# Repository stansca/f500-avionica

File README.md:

# F-500 — projetos do foguete

Repositórios relacionados: [f500-video-2g4](https://github.com/stansca/f500-video-2g4) · [placa-estatico](https://github.com/stansca/placa-estatico) · [rocket-arduino](https://github.com/stansca/rocket-arduino) · [kicad-biblioteca-js](https://github.com/stansca/kicad-biblioteca-js)

Tudo do F-500 (apogeu ~500 m) fica nesta pasta.

## Placas

| Placa | Pasta | Estado |
|---|---|---|
| Aviônica v1 (rayquasa) | [`rayquasa/`](rayquasa/) | final, só THT |
| Aviônica v2 rev. B (câmera DJI/Walksnail) | [`avionica_f500_v2/`](avionica_f500_v2/) | posicionada; **roteamento manual em andamento** |
| Aviônica v2 **rev. C-V** (controle do vídeo 2,4 GHz) | [`avionica_f500_v2_video/`](avionica_f500_v2_video/) | variante da rev. B, roteamento preservado |
| Aviônica v2 rev. C-SV (sem vídeo) | [`avionica_f500_v2_sem_video/`](avionica_f500_v2_sem_video/) | variante da rev. B, roteamento preservado |
| **RF-FEM 2,4 GHz** (vídeo) | [f500-video-2g4 / placa_rf_fem](https://github.com/stansca/f500-video-2g4/tree/main/Hardware/placa_rf_fem) | gerada; cadeia de RF traçada, falta rotear alimentação/controle |
| **Alimentação do vídeo** | [f500-video-2g4 / placa_alim_video](https://github.com/stansca/f500-video-2g4/tree/main/Hardware/placa_alim_video) | gerada; falta rotear |

As duas placas do vídeo ficam dentro de `video_2g4_f500/Hardware/` porque compartilham a biblioteca de símbolos (`Hardware/biblioteca/`) e o gerador (`Hardware/gerador/`). A estrutura segue o padrão dos repositórios da equipe (Hardware / Firmware / Software).

## Sistema de vídeo ao vivo 2,4 GHz

Repositório [f500-video-2g4](https://github.com/stansca/f500-video-2g4) (localmente em `video_2g4_f500/`): placas RF-FEM e de alimentação, software da Pi Zero 2W, dos SDRs (openwifi) e do notebook, e firmware da ESP32.
Documento completo: [Video_2G4_F500_Documentacao.pdf](https://github.com/stansca/f500-video-2g4/blob/main/docs/Video_2G4_F500_Documentacao.pdf).

```
avionica_f500_v2_video (J4) ──XH-4──> placa_alim_video (J2) ──> Pi Zero 2W / ADRV1CRR-BOB / placa_rf_fem
```

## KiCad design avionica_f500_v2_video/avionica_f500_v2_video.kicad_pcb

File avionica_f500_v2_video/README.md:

# Aviônica F-500 v2 — rev. C-V (com vídeo ao vivo 2,4 GHz)

Variante da [rev. B](../avionica_f500_v2/) que leva em conta o documento **"Transmissão de vídeo"** (câmera Global Shutter → Pi Zero 2W → ADRV1CRR-BOB + ADRV9361-Z7035 → FEM SKY85333-11 → filtro ZVBP-2400-S+ → antena Taoglas FXP73, 802.11 OFDM em 2,4 GHz, UDP multicast). A variante sem vídeo está em [`../avionica_f500_v2_sem_video/`](../avionica_f500_v2_sem_video/).

Feita a partir da PCB da rev. B **com o roteamento manual preservado** (`scripts/delta_pcb.py`). Só foram apagadas as trilhas da antiga chave da câmera.

## O que mudou em relação à rev. B (bloco 3)
| rev. B (câmera DJI/Walksnail) | rev. C-V (vídeo do PDF) |
|---|---|
| Q3 AO3401A chaveava VBAT da câmera (até ~1,6 A) pelo J4 | **Removidos Q3, R3, C10, C11.** O vídeo do PDF consome vários ampères em 5 V e **não passa por esta placa** |
| J4: VBAT_CAM, GND, TX, RX | **J4 (JST-XH 4):** 1 `VID_OFF` · 2 GND · 3 `PI_RXD` · 4 `PI_TXD` |
| Q4 AO3400A acionava o gate do Q3 | **Q4 AO3400A em dreno aberto:** com IO4 em HIGH, puxa para GND o pino EN do regulador do vídeo e desliga o vídeo |
| UART direta | **R20/R21 1 kΩ em série** na UART: protegem a Pi quando ela está desligada e a ESP32 transmite (alimentação parasita pelos diodos de proteção) |

**Pinos:** IO4 = `VID_OFF` (antigo CAM_EN), IO25 = `VID_TX` → GPIO15 (RXD) da Pi, IO13 = `VID_RX` ← GPIO14 (TXD) da Pi. Tudo em 3,3 V nos dois lados.

### Por que a alimentação do vídeo fica fora da placa
- **Consumo:** a Pi Zero 2W pede fonte de 5 V/2,5 A. A ADRV1CRR-BOB recebe 5 V e gera os rails do ADRV9361. O PDF diz que o SOM consome 240–820 mA transmitindo. O FEM a +28 dBm consome algumas centenas de mA. Somando, o vídeo precisa de **um regulador 5 V de ≥5 A**.
- **Limite da rev. B:** a chave principal (JST-XH, 3 A), o diodo SS34 (3 A) e o buck MP1584 (3 A) da aviônica não aguentam essa carga.
- **Recomendação:** **bateria 2S própria para o vídeo + regulador 5 V/5 A com pino EN** (ex.: Pololu D36V50F5). O GND do vídeo é ligado ao GND desta placa pelo pino 2 do J4, que é a referência da UART.
- **Independência:** com a ESP32 em reset ou boot, o R4 segura o Q4 desligado e o EN fica solto. **O vídeo funciona mesmo se a aviônica falhar**, e uma falha no vídeo não derruba a recuperação.
- **Confira a lógica do EN do regulador escolhido.** O esperado é EN com pull-up interno, em que nível baixo desliga.

### Desligar sem corromper o SD da Pi
Antes de puxar o `VID_OFF`, a ESP32 manda `SHUTDOWN` pela UART e espera ~10 s. A Pi deve rodar um serviço que lê a serial e executa `poweroff`.

### O que fica em outras placas (conforme o PDF)
- **FEM SKY85333-11** (substituto do SKY85354-11, que foi descontinuado) numa placa de RF própria: microfita/CPW de 50 Ω, LGA 3 × 5 mm. Os sinais de TX/RX enable vêm do SDR, não da ESP32.
- **Filtro de cavidade ZVBP-2400-S+** (SMA) e antena Taoglas FXP73 (U.FL/MHF I), colada em seção radiotransparente.

### Pontos do PDF que precisam de atenção
1. **Canal Wi-Fi:** o filtro passa só **2375–2425 MHz**. Com 20 MHz de largura, só o **canal 1** (2401–2423 MHz) cabe inteiro na banda. Os canais 6 e 11 seriam cortados.
2. **Potência:** o PDF fala em +28 dBm (FEM em MCS0, EIRP 33 dBm) e, em outros trechos, em "1 W (+30 dBm)" (EIRP 35 dBm). As duas ficam abaixo de 36 dBm (Res. ANATEL 680/2017), mas o projeto precisa fixar uma delas e travar a atenuação do AD9361.
3. **Norma:** o texto cita 802.11g/n (OFDM 20 MHz) e, no item do detector, 802.11ax. Vale padronizar em g/n.
4. **Escala:** o PDF mira 4 km de distância, e o F-500 sobe ~500 m. Confira peso e volume (BOB + SOM + Pi + filtro de cavidade + bateria) contra a seção de carga útil.
5. **Interferência:** o PA de 2,4 GHz perto da antena do GPS (1575 MHz) e do LoRa (917 MHz) pode dessensibilizar os receptores. Afaste as antenas e mantenha o Wi-Fi/BT da ESP32 desligado.

## O que mudou para seguir o guia
| Guia | Rev. B |
|---|---|
| Esquemático em blocos, ligados por labels globais | 7 blocos com borda tracejada e título. Dentro de cada bloco, as ligações são fios; entre blocos, labels globais. GND/+5V/+3V3 usam símbolos de alimentação |
| Valor e datasheet dos componentes | Todos têm valor. Os CIs têm datasheet (ESP32, RFM95W, BMP280, MP1584, AO3400A/AO3401A, SS34, microSD) |
| 100 nF junto de cada alimentação | ESP32 (3V3 e 5V), RFM95W (10 µF + 100 nF), BMP280, microSD (10 µF + 100 nF), GPS e saída do buck |
| Regras do fabricante | Configurações do modelo **PCBWay** (2 camadas, 1 oz) importadas no `.kicad_pro`, com o `.kicad_dru` do PCBWay |
| Trilhas pela corrente | Classes de rede (tabela abaixo). Estimativa de corrente anotada no esquemático |
| Até 100 × 100 mm | **60 × 100 mm**: cabe na faixa mais barata e num tubo de ~75 mm |
| Componentes ruidosos longe do rádio | Buck embaixo, LoRa e GPS em cima, separados pelo ESP32. Área sem cobre sob a antena do ESP32 |

## Estimativa de corrente (pior caso)
- **Consumo em 5 V** (via buck): ESP32 250 mA + RFM95W 120 mA + microSD 100 mA + GPS 45 mA + buzzer 30 mA + sensores 6 mA ≈ **550 mA**.
- **Entrada do buck** (80 % de eficiência, 2S descarregada em 6,4 V): **0,54 A**.
- **Vídeo**: alimentado à parte (bateria + regulador 5 V/5 A próprios); por esta placa passam só mA.
- **Pulso do ignitor**: ~3 A.

| Classe | Nets | Trilha |
|---|---|---|
| Bateria | VBAT_IN, VBAT_SW, VBAT, GND | 1,2 mm |
| Pyro | VBAT_ARM, PYRO1_D, PYRO2_D | 1,0 mm |
| Alim_5V / Alim_3V3 | +5V / +3V3 | 0,6 / 0,5 mm |
| RF_50ohm | LORA_ANT | 2,8 mm, curta, com GND em volta |
| Default | sinais | 0,25 mm |

## Peças
- **Montagem:** SMD 0805/SOT-23/SMA com pads *HandSolder*, que dá para soldar no ferro.
- **Módulos:** ESP32-DevKitC, RFM95W, BMP280 e MP1584EN.
- **Conectores:** XT30 para a bateria, bornes de 3,5 mm para os ignitores e JST-XH para chaves, GPS, I2C e vídeo.
- **microSD:** soquete Molex 104031 a 3,3 V direto. Isso elimina o problema de MISO do módulo SD com level shifter.
- **MOSFETs:** AO3400A nos ignitores (pulso de 30 A) e no VID_OFF do vídeo (dreno aberto).
- **Embaixo do DevKit**, que fica em barra fêmea de 8,5 mm, ficam só SMD baixos: o divisor da bateria, os resistores dos LEDs e o driver do buzzer. Há uma regra de DRC que libera essa sobreposição de courtyard.
- Lista completa em `docs/BOM.csv`.

## Estado (09/11/2026)
- ERC: **0 erros** (os mesmos 6 avisos de tipo de pino da rev. B). Paridade esquemático↔PCB: **0**.
- DRC: nenhum tipo de erro novo em relação à rev. B. Continuam os avisos de serigrafia, as ligações por rotear e duas trilhas soltas que já existiam na rev. B (I2C_SDA e um toco de SPI_MOSI).
- Firmware de teste compila (core esp32).

## Antes de fabricar
- **Conferir a furação do módulo MP1584** com o módulo comprado. O footprint `F500v2:MP1584_Modulo` tem pads a ±9,5 × ±6,5 mm, o que é suposição.
- Confirmar a lógica do EN do regulador 5 V/5 A do vídeo e que o tubo comporta 60 × 100 mm e o conjunto de vídeo.
- O firmware não muda em relação à rev. A: use `firmware/pinos_f500_v2.h`. Mande a tensão da bateria por célula para o pacote continuar compatível com o tracker.

## Regenerar
`scripts/delta_pcb.py` aplica mudanças do `design.py` na PCB já roteada sem perder trilhas (é o que gerou esta variante). `scripts/build.sh` gera tudo do zero a partir de `scripts/design.py` (netlist e blocos) e `scripts/pcb_pos.py` (posições). Ele confere a netlist e roda ERC/DRC. **Ele sobrescreve a PCB**: depois de começar a rotear, edite pelo KiCad.

> `docs/Avionica_F-500_v2_Documentacao.pdf` descreve a rev. B, com a câmera DJI. As diferenças estão neste README. O PDF da antena tracker continua válido.

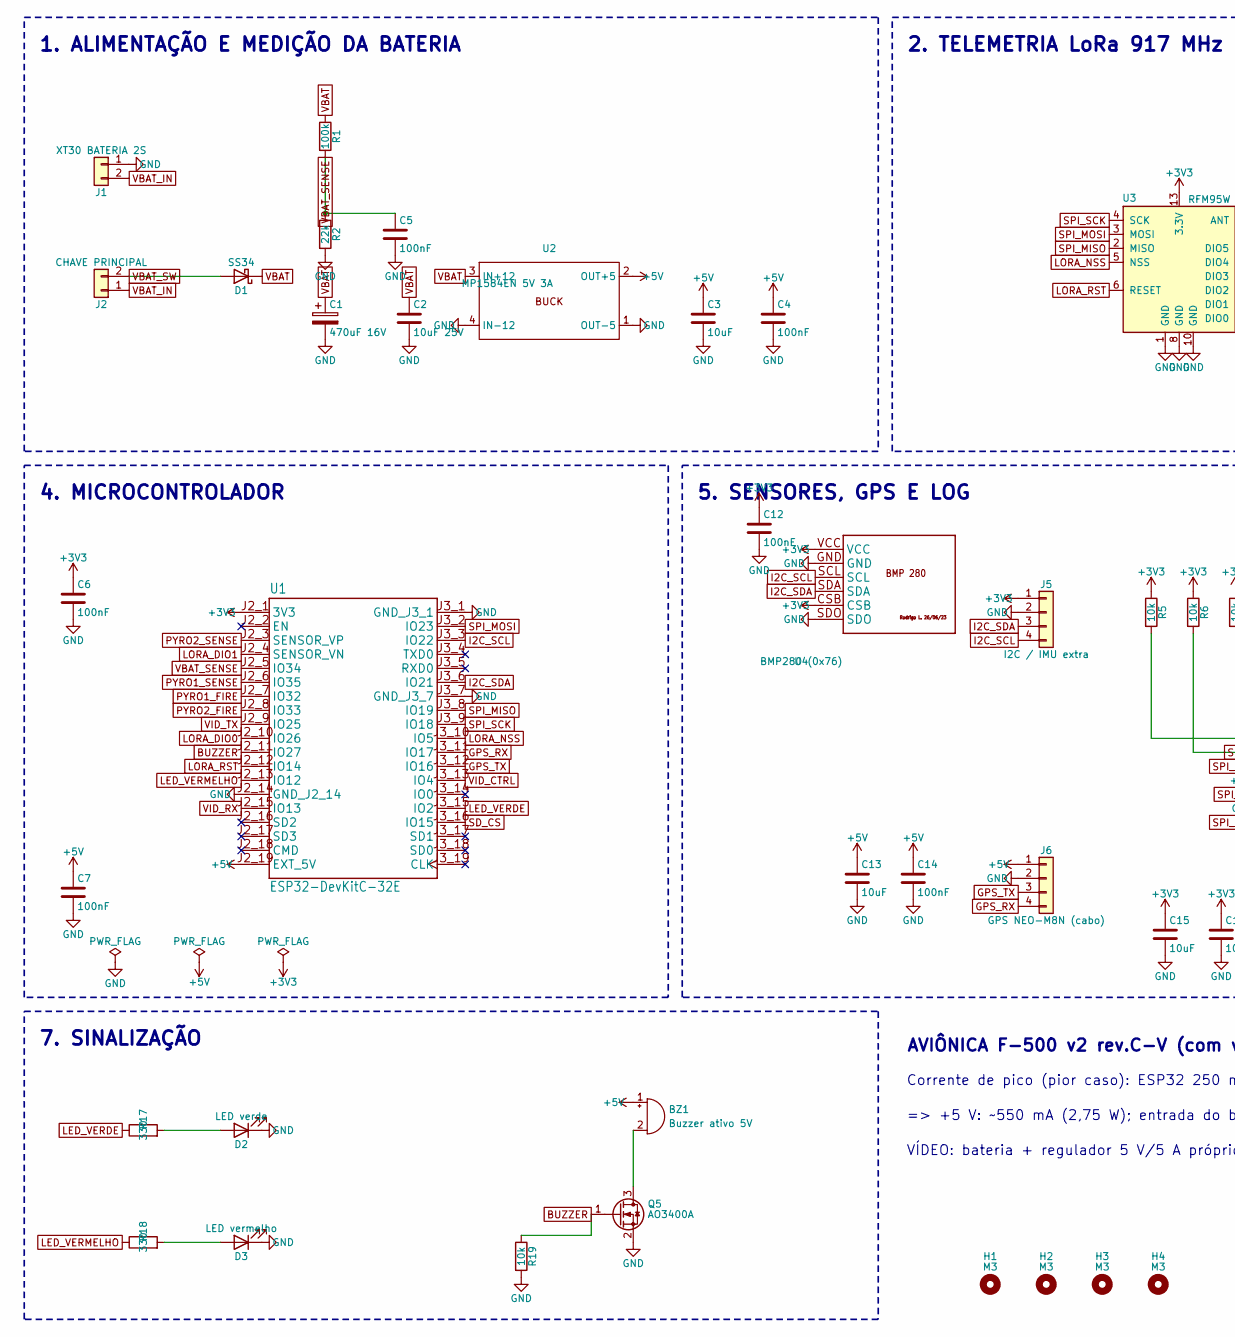
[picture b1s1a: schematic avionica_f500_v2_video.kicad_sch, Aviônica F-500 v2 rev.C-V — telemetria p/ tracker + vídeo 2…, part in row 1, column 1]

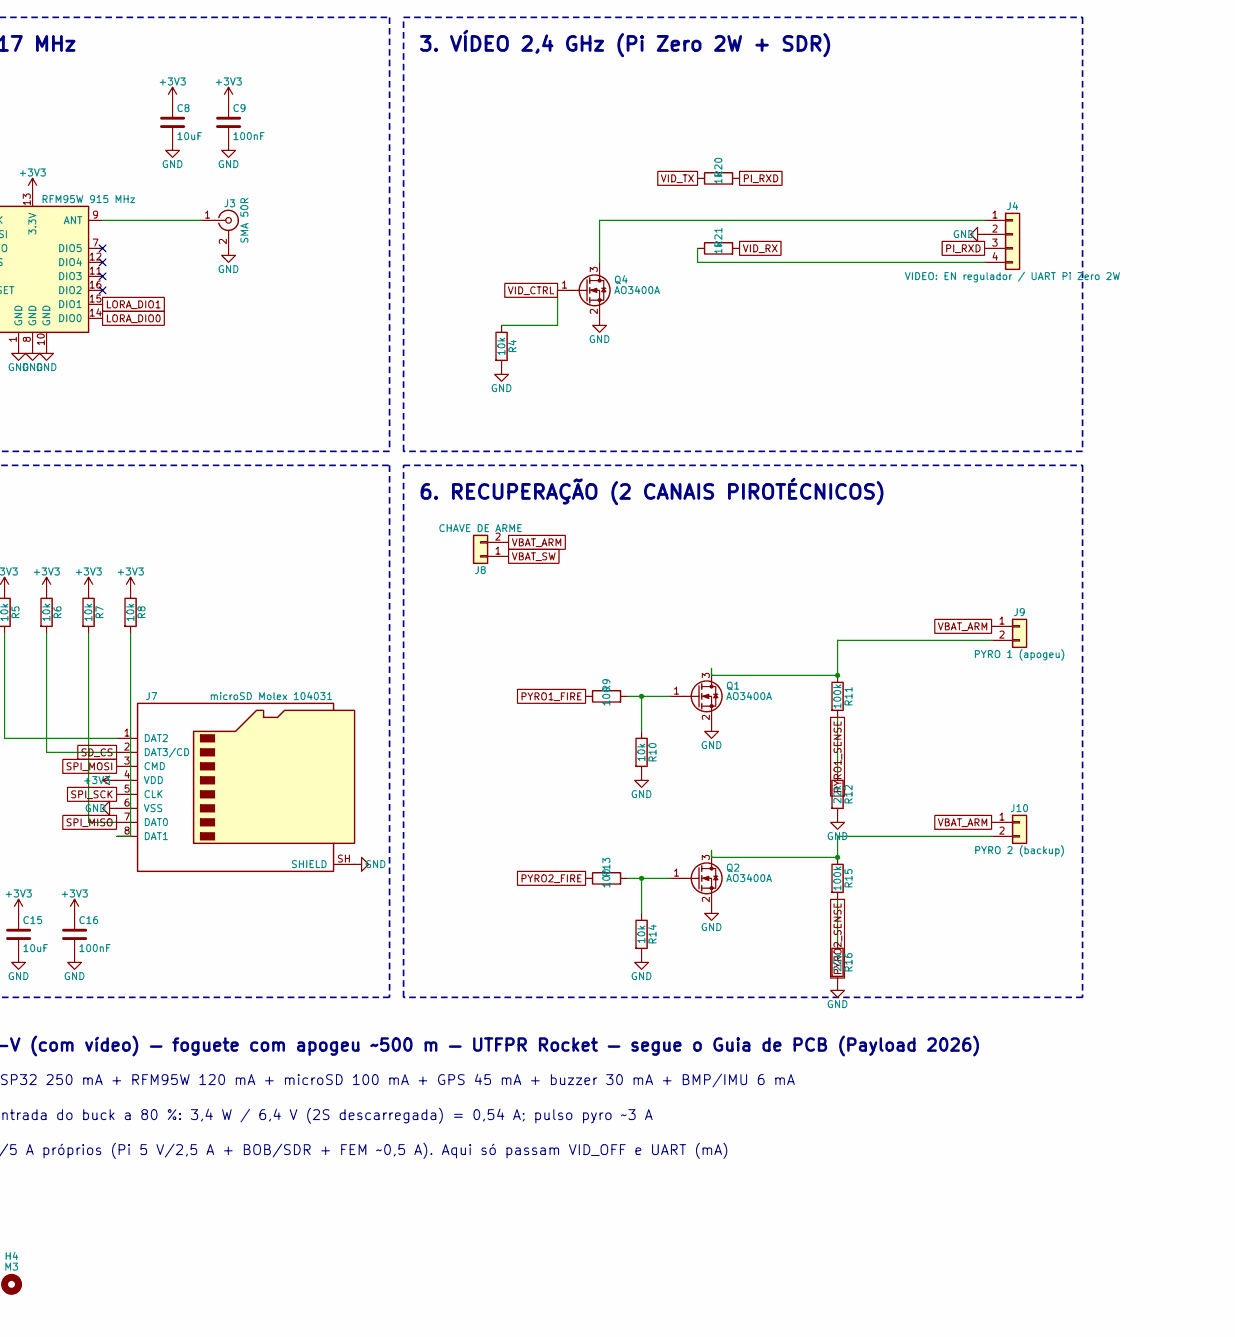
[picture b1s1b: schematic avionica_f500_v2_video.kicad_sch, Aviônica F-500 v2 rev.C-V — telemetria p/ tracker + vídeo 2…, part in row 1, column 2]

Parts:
BZ1: Buzzer ativo 5V; Buzzer_12x9.5RM7.6
C1: 470uF 16V; CP_Radial_D8.0mm_P3.50mm
C2: 10uF 25V; C_1206_3216Metric_Pad1.33x1.80mm_HandSolder
C3: 10uF; C_1206_3216Metric_Pad1.33x1.80mm_HandSolder
C4, C5, C6, C7, C9, C12, C14, C16: 100nF; C_0805_2012Metric_Pad1.18x1.45mm_HandSolder
C8, C13, C15: 10uF; C_0805_2012Metric_Pad1.18x1.45mm_HandSolder
D1: SS34; D_SMA_Handsoldering
D2: LED verde; LED_0805_2012Metric_Pad1.15x1.40mm_HandSolder
D3: LED vermelho; LED_0805_2012Metric_Pad1.15x1.40mm_HandSolder
H1, H2, H3, H4: M3; MountingHole_3.2mm_M3
J1: XT30 BATERIA 2S; AMASS_XT30PW-M_1x02_P2.50mm_Horizontal
J2: CHAVE PRINCIPAL; JST_XH_B2B-XH-A_1x02_P2.50mm_Vertical
J3: SMA 50R; SMA_Amphenol_132289_EdgeMount
J4: VIDEO: EN regulador / UART Pi Zero 2W; JST_XH_B4B-XH-A_1x04_P2.50mm_Vertical
J5: I2C / IMU extra; JST_XH_B4B-XH-A_1x04_P2.50mm_Vertical
J6: GPS NEO-M8N (cabo); JST_XH_B4B-XH-A_1x04_P2.50mm_Vertical
J7: microSD Molex 104031; microSD_HC_Molex_104031-0811
J8: CHAVE DE ARME; JST_XH_B2B-XH-A_1x02_P2.50mm_Vertical
J9: PYRO 1 (apogeu); TerminalBlock_Phoenix_PT-1,5-2-3.5-H_1x02_P3.50mm_Horizontal
J10: PYRO 2 (backup); TerminalBlock_Phoenix_PT-1,5-2-3.5-H_1x02_P3.50mm_Horizontal
Q1, Q2, Q4, Q5: AO3400A; SOT-23
R1, R11, R15: 100k; R_0805_2012Metric_Pad1.20x1.40mm_HandSolder
R2, R12, R16: 22k; R_0805_2012Metric_Pad1.20x1.40mm_HandSolder
R4, R5, R6, R7, R8, R10, R14, R19: 10k; R_0805_2012Metric_Pad1.20x1.40mm_HandSolder
R9, R13: 100; R_0805_2012Metric_Pad1.20x1.40mm_HandSolder
R17, R18: 330; R_0805_2012Metric_Pad1.20x1.40mm_HandSolder
R20, R21: 1k; R_0805_2012Metric_Pad1.20x1.40mm_HandSolder
U1: ESP32-DevKitC-32E
U2: MP1584EN 5V 3A; MP1584_Modulo
U3: RFM95W 915 MHz; HOPERF_RFM9XW_SMD
U4: BMP280 (0x76); BMP280_Modulo

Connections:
+3V3: C6.1, C8.1, C9.1, C12.1, C15.1, C16.1, J5.1, J7.4 (VDD), R5.1, R6.1, R7.1, R8.1, U1.J2_1 (3V3), U3.13 (3.3V), U4.CSB, U4.VCC
+5V: BZ1.1 (+), C3.1, C4.1, C7.1, C13.1, C14.1, J6.1, U1.J2_19 (EXT_5V), U2.2 (OUT+5)
BUZZER: Q5.1 (G), R19.1, U1.J2_11 (IO27)
GND: C1.2, C2.2, C3.2, C4.2, C5.2, C6.2, C7.2, C8.2, C9.2, C12.2, C13.2, C14.2, C15.2, C16.2, D2.1 (K), D3.1 (K), J1.1, J3.2 (Ext), J4.2, J5.2, J6.2, J7.6 (VSS), J7.SH (SHIELD), Q1.2 (S), Q2.2 (S), Q4.2 (S), Q5.2 (S), R2.2, R4.2, R10.2, R12.2, R14.2, R16.2, R19.2, U1.J2_14 (GND_J2_14), U1.J3_1 (GND_J3_1), U1.J3_7 (GND_J3_7), U2.1 (OUT-5), U2.4 (IN-12), U3.1 (GND), U3.8 (GND), U3.10 (GND), U4.GND, U4.SDO
GPS_RX: J6.4, U1.J3_11 (IO17)
GPS_TX: J6.3, U1.J3_12 (IO16)
I2C_SCL: J5.4, U1.J3_3 (IO22), U4.SCL
I2C_SDA: J5.3, U1.J3_6 (IO21), U4.SDA
LED_VERDE: R17.1, U1.J3_15 (IO2)
LED_VERMELHO: R18.1, U1.J2_13 (IO12)
LORA_DIO0: U1.J2_10 (IO26), U3.14 (DIO0)
LORA_DIO1: U1.J2_4 (SENSOR_VN), U3.15 (DIO1)
LORA_NSS: U1.J3_10 (IO5), U3.5 (NSS)
LORA_RST: U1.J2_12 (IO14), U3.6 (RESET)
unnamed: BZ1.2 (-), Q5.3 (D)
unnamed: D2.2 (A), R17.2
unnamed: D3.2 (A), R18.2
unnamed: J3.1 (In), U3.9 (ANT)
unnamed: J4.1, Q4.3 (D)
unnamed: J4.4, R21.1
unnamed: J7.8 (DAT1), R8.2
unnamed: J7.1 (DAT2), R5.2
unnamed: J9.2, Q1.3 (D), R11.1
unnamed: J10.2, Q2.3 (D), R15.1
unnamed: Q1.1 (G), R9.2, R10.1
unnamed: Q2.1 (G), R13.2, R14.1
PI_RXD: J4.3, R20.2
PYRO1_FIRE: R9.1, U1.J2_7 (IO32)
PYRO1_SENSE: R11.2, R12.1, U1.J2_6 (IO35)
PYRO2_FIRE: R13.1, U1.J2_8 (IO33)
PYRO2_SENSE: R15.2, R16.1, U1.J2_3 (SENSOR_VP)
SD_CS: J7.2 (DAT3/CD), R6.2, U1.J3_16 (IO15)
SPI_MISO: J7.7 (DAT0), R7.2, U1.J3_8 (IO19), U3.2 (MISO)
SPI_MOSI: J7.3 (CMD), U1.J3_2 (IO23), U3.3 (MOSI)
SPI_SCK: J7.5 (CLK), U1.J3_9 (IO18), U3.4 (SCK)
VBAT: C1.1, C2.1, D1.1 (K), R1.1, U2.3 (IN+12)
VBAT_ARM: J8.2, J9.1, J10.1
VBAT_IN: J1.2, J2.1
VBAT_SENSE: C5.1, R1.2, R2.1, U1.J2_5 (IO34)
VBAT_SW: D1.2 (A), J2.2, J8.1
VID_CTRL: Q4.1 (G), R4.1, U1.J3_13 (IO4)
VID_RX: R21.2, U1.J2_15 (IO13)
VID_TX: R20.1, U1.J2_9 (IO25)

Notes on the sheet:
1. ALIMENTAÇÃO E MEDIÇÃO DA BATERIA
2. TELEMETRIA LoRa 917 MHz
3. VÍDEO 2,4 GHz (Pi Zero 2W + SDR)
4. MICROCONTROLADOR
5. SENSORES, GPS E LOG
6. RECUPERAÇÃO (2 CANAIS PIROTÉCNICOS)
7. SINALIZAÇÃO
AVIÔNICA F-500 v2 rev.C-V (com vídeo) — foguete com apogeu ~500 m — UTFPR Rocket — segue o Guia de PCB (Payload 2026)
Corrente de pico (pior caso): ESP32 250 mA + RFM95W 120 mA + microSD 100 mA + GPS 45 mA + buzzer 30 mA + BMP/IMU 6 mA
=> +5 V: ~550 mA (2,75 W); entrada do buck a 80 %: 3,4 W / 6,4 V (2S descarregada) = 0,54 A; pulso pyro ~3 A
VÍDEO: bateria + regulador 5 V/5 A próprios (Pi 5 V/2,5 A + BOB/SDR + FEM ~0,5 A). Aqui só passam VID_OFF e UART (mA)

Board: 2 copper layers, 60 parts (0 on the bottom side), 43 nets, no tracks yet.

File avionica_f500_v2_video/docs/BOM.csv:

"Reference","Value","Footprint","QUANTITY"
"BZ1","Buzzer ativo 5V","Buzzer_Beeper:Buzzer_12x9.5RM7.6","1"
"C1","470uF 16V","Capacitor_THT:CP_Radial_D8.0mm_P3.50mm","1"
"C2","10uF 25V","Capacitor_SMD:C_1206_3216Metric_Pad1.33x1.80mm_HandSolder","1"
"C3","10uF","Capacitor_SMD:C_1206_3216Metric_Pad1.33x1.80mm_HandSolder","1"
"C4-C7,C9,C12,C14,C16","100nF","Capacitor_SMD:C_0805_2012Metric_Pad1.18x1.45mm_HandSolder","8"
"C8,C13,C15","10uF","Capacitor_SMD:C_0805_2012Metric_Pad1.18x1.45mm_HandSolder","3"
"D1","SS34","Diode_SMD:D_SMA_Handsoldering","1"
"D2","LED verde","LED_SMD:LED_0805_2012Metric_Pad1.15x1.40mm_HandSolder","1"
"D3","LED vermelho","LED_SMD:LED_0805_2012Metric_Pad1.15x1.40mm_HandSolder","1"
"J1","XT30 BATERIA 2S","Connector_AMASS:AMASS_XT30PW-M_1x02_P2.50mm_Horizontal","1"
"J2","CHAVE PRINCIPAL","Connector_JST:JST_XH_B2B-XH-A_1x02_P2.50mm_Vertical","1"
"J3","SMA 50R","Connector_Coaxial:SMA_Amphenol_132289_EdgeMount","1"
"J4","VIDEO: EN regulador / UART Pi Zero 2W","Connector_JST:JST_XH_B4B-XH-A_1x04_P2.50mm_Vertical","1"
"J5","I2C / IMU extra","Connector_JST:JST_XH_B4B-XH-A_1x04_P2.50mm_Vertical","1"
"J6","GPS NEO-M8N (cabo)","Connector_JST:JST_XH_B4B-XH-A_1x04_P2.50mm_Vertical","1"
"J7","microSD Molex 104031","Connector_Card:microSD_HC_Molex_104031-0811","1"
"J8","CHAVE DE ARME","Connector_JST:JST_XH_B2B-XH-A_1x02_P2.50mm_Vertical","1"
"J9","PYRO 1 (apogeu)","TerminalBlock_Phoenix:TerminalBlock_Phoenix_PT-1,5-2-3.5-H_1x02_P3.50mm_Horizontal","1"
"J10","PYRO 2 (backup)","TerminalBlock_Phoenix:TerminalBlock_Phoenix_PT-1,5-2-3.5-H_1x02_P3.50mm_Horizontal","1"
"Q1,Q2,Q4,Q5","AO3400A","Package_TO_SOT_SMD:SOT-23","4"
"R1,R11,R15","100k","Resistor_SMD:R_0805_2012Metric_Pad1.20x1.40mm_HandSolder","3"
"R2,R12,R16","22k","Resistor_SMD:R_0805_2012Metric_Pad1.20x1.40mm_HandSolder","3"
"R4-R8,R10,R14,R19","10k","Resistor_SMD:R_0805_2012Metric_Pad1.20x1.40mm_HandSolder","8"
"R9,R13","100","Resistor_SMD:R_0805_2012Metric_Pad1.20x1.40mm_HandSolder","2"
"R17,R18","330","Resistor_SMD:R_0805_2012Metric_Pad1.20x1.40mm_HandSolder","2"
"R20,R21","1k","Resistor_SMD:R_0805_2012Metric_Pad1.20x1.40mm_HandSolder","2"
"U1","ESP32-DevKitC-32E","JS_Microcontroladores:ESP32-DevKitC-32E","1"
"U2","MP1584EN 5V 3A","F500v2:MP1584_Modulo","1"
"U3","RFM95W 915 MHz","RF_Module:HOPERF_RFM9XW_SMD","1"
"U4","BMP280 (0x76)","JS_Sensores:BMP280_Modulo","1"

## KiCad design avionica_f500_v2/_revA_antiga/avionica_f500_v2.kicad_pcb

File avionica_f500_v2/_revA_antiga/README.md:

# Aviônica F-500 v2

Computador de bordo para o foguete F-500 (apogeu de ~500 m). É a evolução da `rayquasa` (F-500 v1) com:

- **Telemetria compatível com a antena tracker**: RFM95W (SX1276) a 917 MHz nos **mesmos GPIOs do `tracker_rx`**, com o mesmo pacote de 26 bytes a 5 Hz.
- **Câmera/VTX digital**: conector próprio com VBAT 2S chaveado pelo ESP32 e UART para MSP/OSD.
- **2 canais de recuperação** com MOSFET de porta lógica, leitura de continuidade e chave de arme física.
- GPS por cabo, BMP280, microSD para log e conector I2C extra para IMU.

PCB de 2 camadas, **60 × 170 mm**, quase tudo THT ou módulo. A única peça SMD é o RFM95W, que tem bordas castelladas e dá para soldar no ferro. Os furos M3 ficam nas posições H1–H4.

## Arquivos
| Arquivo | O que é |
|---|---|
| `avionica_f500_v2.kicad_sch/.kicad_pcb/.kicad_pro` | Projeto KiCad 10 |
| `docs/esquematico.pdf`, `docs/pcb_*.png`, `docs/BOM.csv` | Saídas para revisão e compra |
| `firmware/pinos_f500_v2.h` | Pinagem para portar o `foguete_tx.ino` |
| `scripts/` | Gerador (`design.py` = netlist + posições). `build.sh` regenera **e sobrescreve a PCB** |

## Estado
- ERC: 0 erros. Ficam 7 avisos de tipo de pino, que vêm dos símbolos de módulo da biblioteca JS.
- Paridade esquemático ↔ PCB: 0 problemas.
- **Falta rotear.** São 71 ligações em ratsnest. Os planos de GND nas duas faces já estão criados.
- O DRC acusa 5 violações de "borda" no J3. Isso é esperado, porque o SMA de borda precisa encostar na borda. Exclua essas violações no DRC do KiCad. Os avisos de serigrafia sobre pad vêm dos footprints da biblioteca.

### Roteamento sugerido
1. Abra no KiCad. As classes de rede já estão configuradas: Potência com 1,0 mm (VBAT*, PYRO*_D, +5V, GND), 3V3 com 0,6 mm e RF com 2,8 mm.
2. Rote primeiro **à mão**: LORA_ANT (do pino 9 do RFM até o SMA, curto e reto, com GND dos dois lados), VBAT_SW→ARM→PYRO, VBAT→Q3→J9.
3. O resto pode ir no Freerouting (plugin do KiCad) ou à mão. Depois, preencha as zonas (B).

## Pinagem (ESP32-DevKitC)
| Função | GPIO | Observação |
|---|---|---|
| LoRa SCK/MISO/MOSI/NSS | 18/19/23/5 | igual ao tracker_rx |
| LoRa DIO0 / RST / DIO1 | 26 / 14 / 39 | |
| microSD CS | 15 | SPI compartilhado |
| GPS RX/TX (UART2) | 16/17 | conector J5 (5 V) |
| I2C SDA/SCL | 21/22 | BMP280 0x76 + J4 |
| CAM_EN / CAM TX / CAM RX | 4 / 25 / 13 | J9 |
| PYRO1 / PYRO2 | 32 / 33 | pinos sem função de boot (sem disparo no boot) |
| Continuidade PYRO1 / PYRO2 | 35 / 36 | só entrada |
| VBAT (÷5,545) | 34 | |
| LED verde / vermelho / buzzer | 2 / 12 / 27 | o LED + resistor mantém o IO12 em nível baixo no boot |

## Câmera que filma e transmite
O conector **J9** entrega VBAT 2S (6,4–8,4 V), GND, TX e RX. O ESP32 liga a alimentação pelo `CAM_EN` (P-MOSFET IRF9540N), então dá para deixar a câmera desligada na rampa e ligar só na contagem. A UART serve para emular MSP e mostrar altitude/velocidade no OSD ou acionar a gravação.

Opções, da mais completa para a mais barata:
1. **DJI O4 Air Unit / O4 Pro**: grava em alta resolução no próprio módulo e transmite digital para os óculos DJI. Os óculos têm saída para celular/PC, o que permite fazer live.
2. **Walksnail Avatar HD**: mesma ideia, mais barato.
3. **Câmera FPV analógica + VTX 5,8 GHz + gravação separada** (tipo RunCam Split): imagem pior, mas é barato e tem latência zero.

Confira no datasheet se a faixa de entrada do modelo escolhido aceita 2S. A antena do VTX precisa ficar numa seção **não condutiva** (fibra de vidro/papelão; fibra de carbono e alumínio bloqueiam) e longe da antena LoRa. O VTX esquenta muito sem fluxo de ar, então ligue só perto do lançamento.

## Antes de fabricar
- Confirme as dimensões físicas dos módulos (buck LM2596, SD, BMP280) com as peças que vocês têm.
- Confira se o tubo/sled comporta 60 × 170 mm.
- Os TO-220 de pé podem ser dobrados deitados para aguentar melhor a aceleração. Prenda os módulos com abraçadeira ou cola quente.
- O módulo de SD com level shifter às vezes não libera o MISO. Se o LoRa falhar com o SD encaixado, use um módulo sem shifter (3,3 V direto).

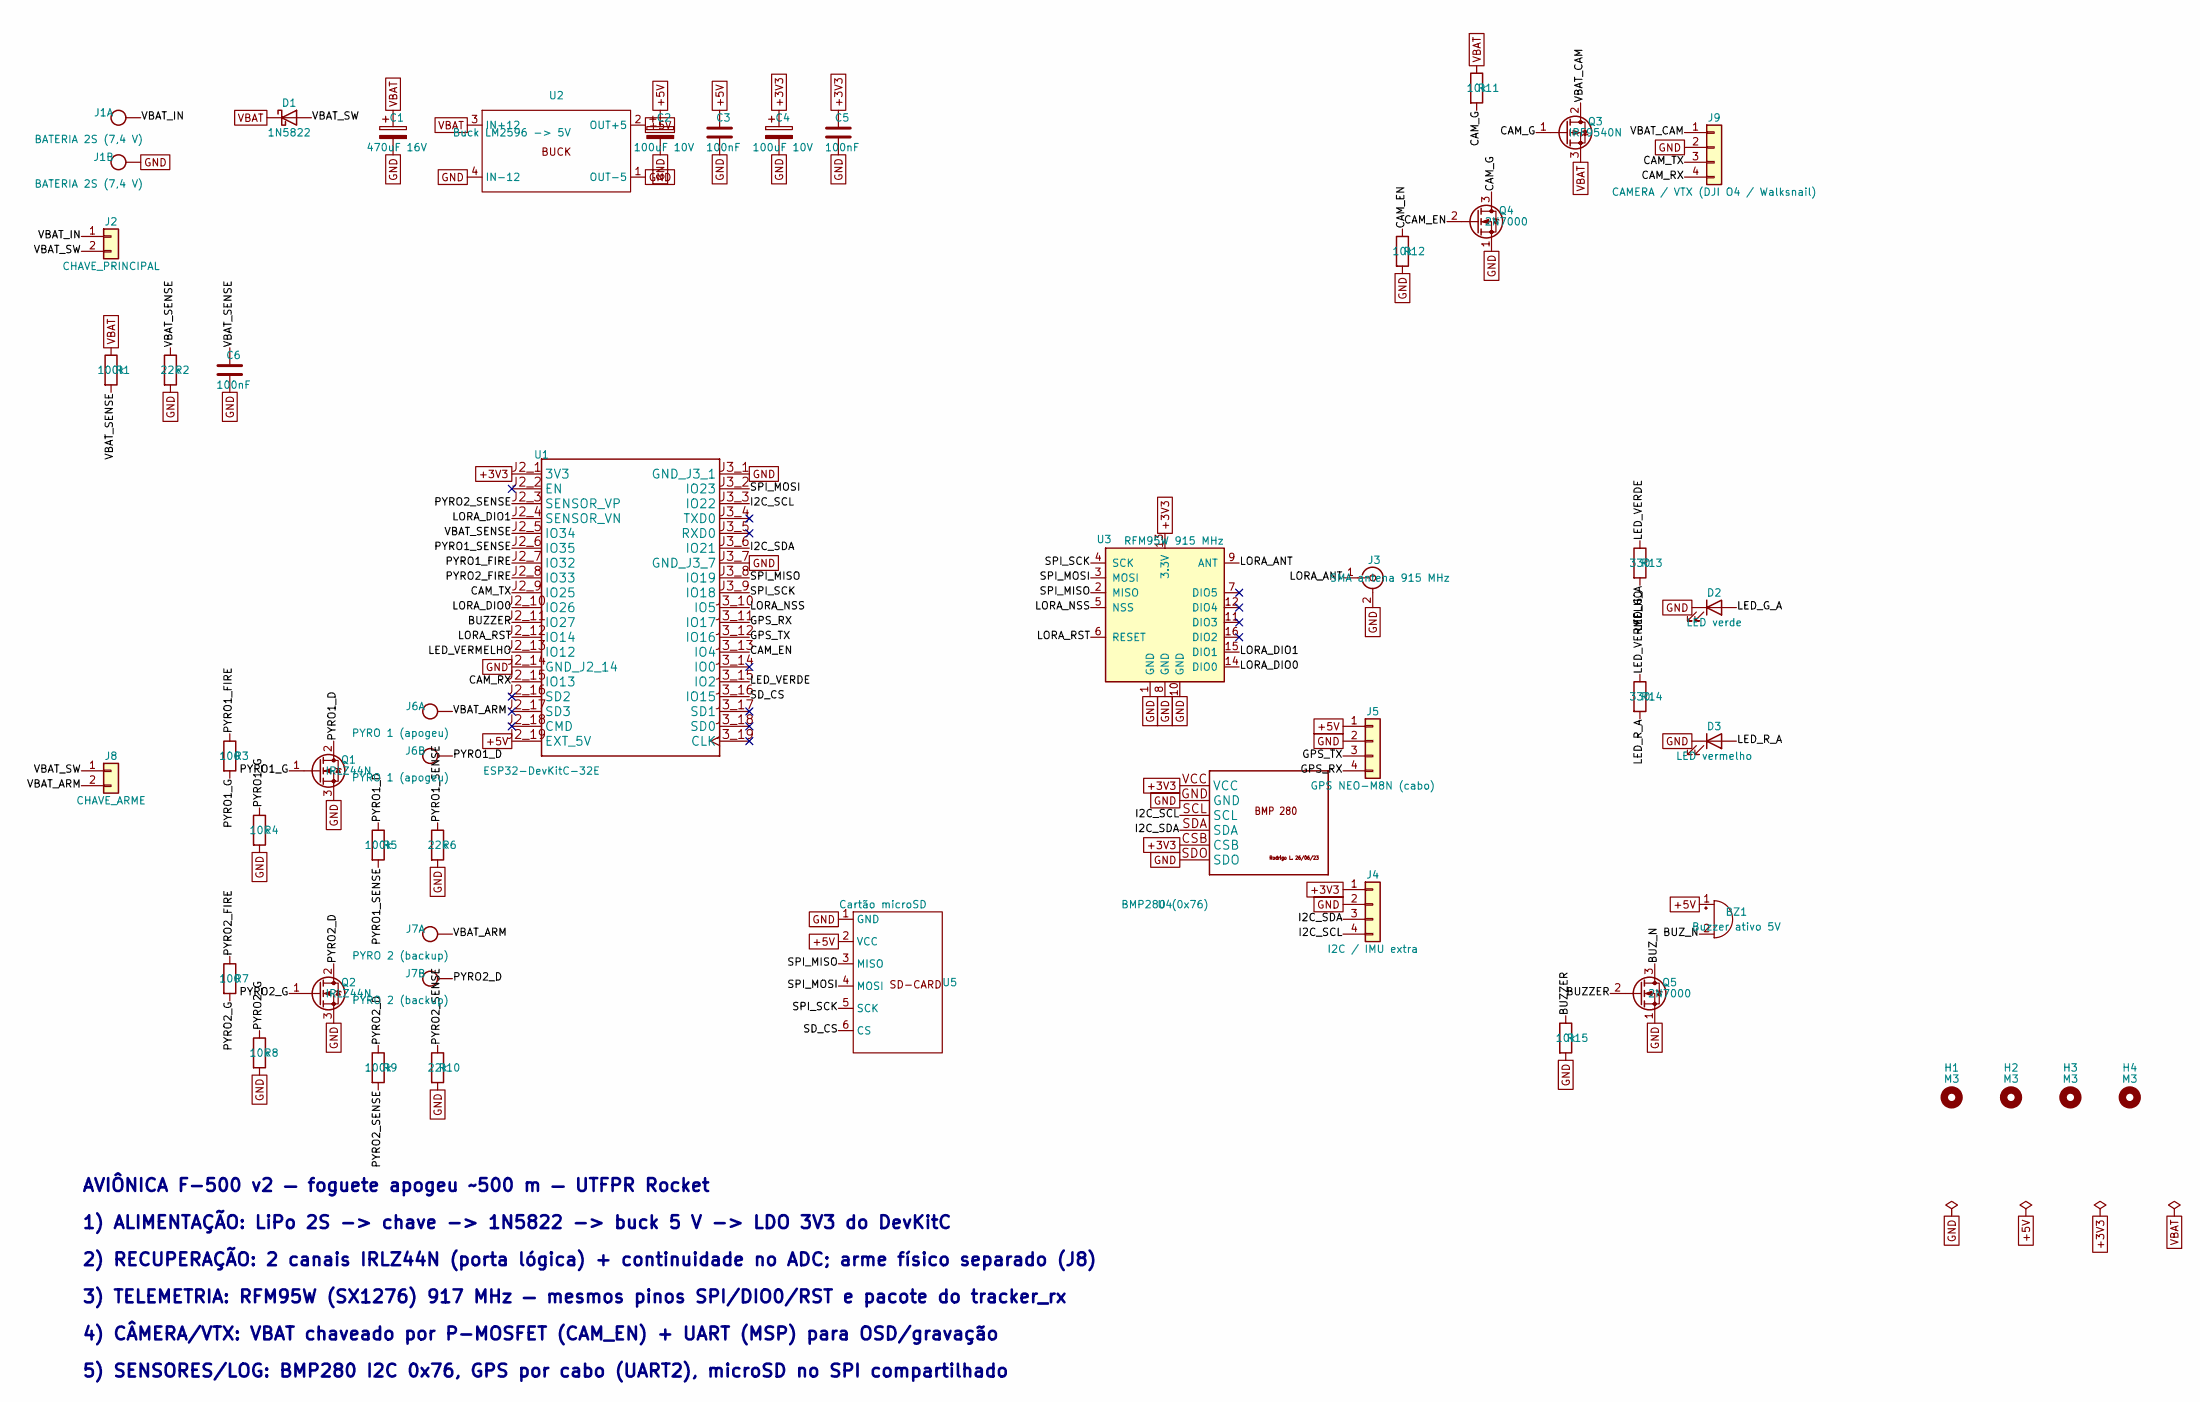
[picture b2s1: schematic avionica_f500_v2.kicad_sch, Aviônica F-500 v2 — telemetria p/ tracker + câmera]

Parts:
BZ1: Buzzer ativo 5V; Buzzer_12x9.5RM7.6
C1: 470uF 16V; CP_Radial_D8.0mm_P3.50mm
C2, C4: 100uF 10V; CP_Radial_D6.3mm_P2.50mm
C3, C5, C6: 100nF; C_Disc_D3.0mm_W2.0mm_P2.50mm
D1: 1N5822; D_DO-201AD_P15.24mm_Horizontal
D2: LED verde; LED_D3.0mm
D3: LED vermelho; LED_D3.0mm
H1, H2, H3, H4: M3; MountingHole_3.2mm_M3
J1: BATERIA 2S (7,4 V); Borne_AK500-2
J2: CHAVE_PRINCIPAL; JST_XH_B2B-XH-A_1x02_P2.50mm_Vertical
J3: SMA antena 915 MHz; SMA_Amphenol_132289_EdgeMount
J4: I2C / IMU extra; JST_XH_B4B-XH-A_1x04_P2.50mm_Vertical
J5: GPS NEO-M8N (cabo); JST_XH_B4B-XH-A_1x04_P2.50mm_Vertical
J6: PYRO 1 (apogeu); Borne_AK500-2
J7: PYRO 2 (backup); Borne_AK500-2
J8: CHAVE_ARME; JST_XH_B2B-XH-A_1x02_P2.50mm_Vertical
J9: CAMERA / VTX (DJI O4 / Walksnail); JST_XH_B4B-XH-A_1x04_P2.50mm_Vertical
Q1, Q2: IRLZ44N; TO-220-3_Vertical
Q3: IRF9540N; TO-220-3_Vertical
Q4, Q5: 2N7000; TO-92_Inline
R1, R5, R9: 100k; R_Axial_DIN0207_L6.3mm_D2.5mm_P7.62mm_Horizontal
R2, R6, R10: 22k; R_Axial_DIN0207_L6.3mm_D2.5mm_P7.62mm_Horizontal
R3, R7: 100; R_Axial_DIN0207_L6.3mm_D2.5mm_P7.62mm_Horizontal
R4, R8, R11, R12, R15: 10k; R_Axial_DIN0207_L6.3mm_D2.5mm_P7.62mm_Horizontal
R13, R14: 330; R_Axial_DIN0207_L6.3mm_D2.5mm_P7.62mm_Horizontal
U1: ESP32-DevKitC-32E
U2: Buck LM2596 -> 5V; Buck_Conversor
U3: RFM95W 915 MHz; HOPERF_RFM9XW_SMD
U4: BMP280 (0x76); BMP280_Modulo
U5: Cartão microSD; SD_Card_Adapter

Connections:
+3V3: C4.1, C5.1, J4.1, U1.J2_1 (3V3), U3.13 (3.3V), U4.CSB, U4.VCC
+5V: BZ1.1 (+), C2.1, C3.1, J5.1, U1.J2_19 (EXT_5V), U2.2 (OUT+5), U5.2 (VCC)
/BUZZER: Q5.2 (G), R15.1, U1.J2_11 (IO27)
/BUZ_N: BZ1.2 (-), Q5.3 (D)
/CAM_EN: Q4.2 (G), R12.1, U1.J3_13 (IO4)
/CAM_G: Q3.1 (G), Q4.3 (D), R11.2
/CAM_RX: J9.4, U1.J2_15 (IO13)
/CAM_TX: J9.3, U1.J2_9 (IO25)
/GPS_RX: J5.4, U1.J3_11 (IO17)
/GPS_TX: J5.3, U1.J3_12 (IO16)
/I2C_SCL: J4.4, U1.J3_3 (IO22), U4.SCL
/I2C_SDA: J4.3, U1.J3_6 (IO21), U4.SDA
/LED_G_A: D2.2 (A), R13.2
/LED_R_A: D3.2 (A), R14.2
/LED_VERDE: R13.1, U1.J3_15 (IO2)
/LED_VERMELHO: R14.1, U1.J2_13 (IO12)
/LORA_ANT: J3.1 (In), U3.9 (ANT)
/LORA_DIO0: U1.J2_10 (IO26), U3.14 (DIO0)
/LORA_DIO1: U1.J2_4 (SENSOR_VN), U3.15 (DIO1)
/LORA_NSS: U1.J3_10 (IO5), U3.5 (NSS)
/LORA_RST: U1.J2_12 (IO14), U3.6 (RESET)
/PYRO1_D: J6.2, Q1.2 (D), R5.1
/PYRO1_FIRE: R3.1, U1.J2_7 (IO32)
/PYRO1_G: Q1.1 (G), R3.2, R4.1
/PYRO1_SENSE: R5.2, R6.1, U1.J2_6 (IO35)
/PYRO2_D: J7.2, Q2.2 (D), R9.1
/PYRO2_FIRE: R7.1, U1.J2_8 (IO33)
/PYRO2_G: Q2.1 (G), R7.2, R8.1
/PYRO2_SENSE: R9.2, R10.1, U1.J2_3 (SENSOR_VP)
/SD_CS: U1.J3_16 (IO15), U5.6 (CS)
/SPI_MISO: U1.J3_8 (IO19), U3.2 (MISO), U5.3 (MISO)
/SPI_MOSI: U1.J3_2 (IO23), U3.3 (MOSI), U5.4 (MOSI)
/SPI_SCK: U1.J3_9 (IO18), U3.4 (SCK), U5.5 (SCK)
/VBAT_ARM: J6.1, J7.1, J8.2
/VBAT_CAM: J9.1, Q3.2 (D)
/VBAT_IN: J1.1, J2.1
/VBAT_SENSE: C6.1, R1.2, R2.1, U1.J2_5 (IO34)
/VBAT_SW: D1.2 (A), J2.2, J8.1
GND: C1.2, C2.2, C3.2, C4.2, C5.2, C6.2, D2.1 (K), D3.1 (K), J1.2, J3.2 (Ext), J4.2, J5.2, J9.2, Q1.3 (S), Q2.3 (S), Q4.1 (S), Q5.1 (S), R2.2, R4.2, R6.2, R8.2, R10.2, R12.2, R15.2, U1.J2_14 (GND_J2_14), U1.J3_1 (GND_J3_1), U1.J3_7 (GND_J3_7), U2.1 (OUT-5), U2.4 (IN-12), U3.1 (GND), U3.8 (GND), U3.10 (GND), U4.GND, U4.SDO, U5.1 (GND)
VBAT: C1.1, D1.1 (K), Q3.3 (S), R1.1, R11.1, U2.3 (IN+12)

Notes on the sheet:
AVIÔNICA F-500 v2 — foguete apogeu ~500 m — UTFPR Rocket
1) ALIMENTAÇÃO: LiPo 2S -> chave -> 1N5822 -> buck 5 V -> LDO 3V3 do DevKitC
2) RECUPERAÇÃO: 2 canais IRLZ44N (porta lógica) + continuidade no ADC; arme físico separado (J8)
3) TELEMETRIA: RFM95W (SX1276) 917 MHz — mesmos pinos SPI/DIO0/RST e pacote do tracker_rx
4) CÂMERA/VTX: VBAT chaveado por P-MOSFET (CAM_EN) + UART (MSP) para OSD/gravação
5) SENSORES/LOG: BMP280 I2C 0x76, GPS por cabo (UART2), microSD no SPI compartilhado

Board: 2 copper layers, 48 parts (0 on the bottom side), 40 nets, no tracks yet.

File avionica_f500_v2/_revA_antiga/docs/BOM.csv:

"Reference","Value","Footprint","QUANTITY"
"BZ1","Buzzer ativo 5V","Buzzer_Beeper:Buzzer_12x9.5RM7.6","1"
"C1","470uF 16V","Capacitor_THT:CP_Radial_D8.0mm_P3.50mm","1"
"C2,C4","100uF 10V","Capacitor_THT:CP_Radial_D6.3mm_P2.50mm","2"
"C3,C5,C6","100nF","Capacitor_THT:C_Disc_D3.0mm_W2.0mm_P2.50mm","3"
"D1","1N5822","Diode_THT:D_DO-201AD_P15.24mm_Horizontal","1"
"D2","LED verde","LED_THT:LED_D3.0mm","1"
"D3","LED vermelho","LED_THT:LED_D3.0mm","1"
"J1","BATERIA 2S (7,4 V)","JS_Conectores:Borne_AK500-2","1"
"J2","CHAVE_PRINCIPAL","Connector_JST:JST_XH_B2B-XH-A_1x02_P2.50mm_Vertical","1"
"J3","SMA antena 915 MHz","Connector_Coaxial:SMA_Amphenol_132289_EdgeMount","1"
"J4","I2C / IMU extra","Connector_JST:JST_XH_B4B-XH-A_1x04_P2.50mm_Vertical","1"
"J5","GPS NEO-M8N (cabo)","Connector_JST:JST_XH_B4B-XH-A_1x04_P2.50mm_Vertical","1"
"J6","PYRO 1 (apogeu)","JS_Conectores:Borne_AK500-2","1"
"J7","PYRO 2 (backup)","JS_Conectores:Borne_AK500-2","1"
"J8","CHAVE_ARME","Connector_JST:JST_XH_B2B-XH-A_1x02_P2.50mm_Vertical","1"
"J9","CAMERA / VTX (DJI O4 / Walksnail)","Connector_JST:JST_XH_B4B-XH-A_1x04_P2.50mm_Vertical","1"
"Q1,Q2","IRLZ44N","Package_TO_SOT_THT:TO-220-3_Vertical","2"
"Q3","IRF9540N","Package_TO_SOT_THT:TO-220-3_Vertical","1"
"Q4,Q5","2N7000","Package_TO_SOT_THT:TO-92_Inline","2"
"R1,R5,R9","100k","Resistor_THT:R_Axial_DIN0207_L6.3mm_D2.5mm_P7.62mm_Horizontal","3"
"R2,R6,R10","22k","Resistor_THT:R_Axial_DIN0207_L6.3mm_D2.5mm_P7.62mm_Horizontal","3"
"R3,R7","100","Resistor_THT:R_Axial_DIN0207_L6.3mm_D2.5mm_P7.62mm_Horizontal","2"
"R4,R8,R11,R12,R15","10k","Resistor_THT:R_Axial_DIN0207_L6.3mm_D2.5mm_P7.62mm_Horizontal","5"
"R13,R14","330","Resistor_THT:R_Axial_DIN0207_L6.3mm_D2.5mm_P7.62mm_Horizontal","2"
"U1","ESP32-DevKitC-32E","JS_Microcontroladores:ESP32-DevKitC-32E","1"
"U2","Buck LM2596 -> 5V","JS_Energia:Buck_Conversor","1"
"U3","RFM95W 915 MHz","RF_Module:HOPERF_RFM9XW_SMD","1"
"U4","BMP280 (0x76)","JS_Sensores:BMP280_Modulo","1"
"U5","Cartão microSD","JS_Modulos:SD_Card_Adapter","1"

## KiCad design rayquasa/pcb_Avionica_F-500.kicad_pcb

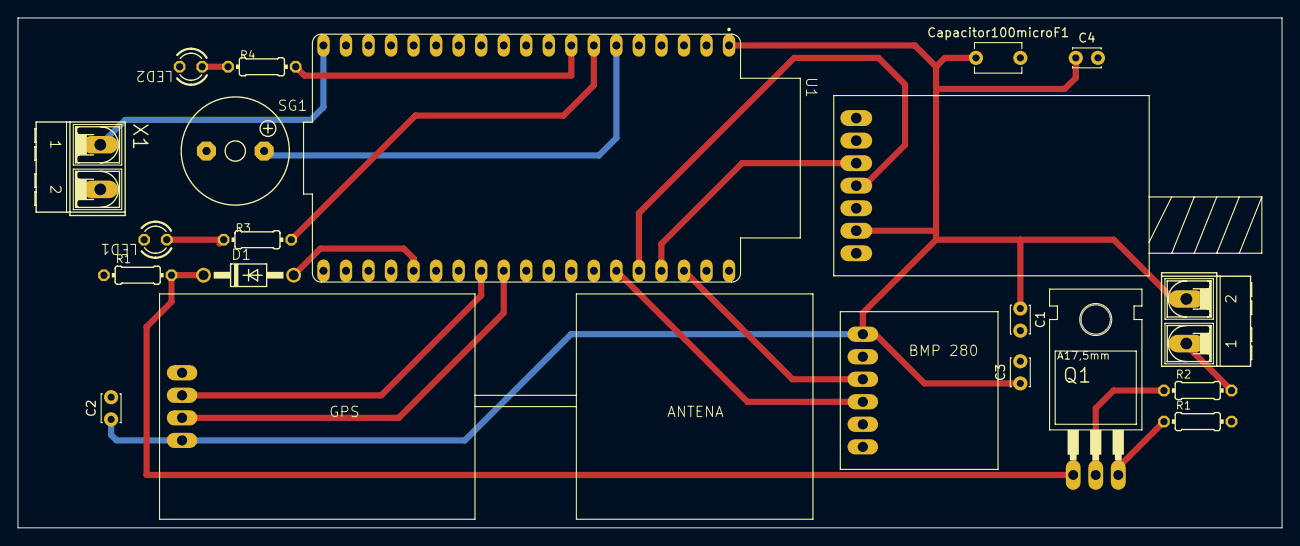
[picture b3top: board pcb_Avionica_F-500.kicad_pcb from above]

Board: 2 copper layers, 142.5 x 57.5 mm, 21 parts (0 on the bottom side), 19 nets.

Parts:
C1, C2, C3, C4: C_Small; C_Disc_D3.0mm_W2.0mm_P2.50mm
Capacitor100microF1: C; C_Disc_D5.1mm_W3.2mm_P5.00mm
D1: 1N4004; DO41-10
LED1, LED2: TLLR4400; LED_3mm
Q1: IRF620; TO220
R1, R1#2, R2, R3, R4: R_Axial_0204-7
SG1: F/QMX; Buzzer_F-QMX
U1: ESP32-DevKitC-32E
U$1: BMP280; BMP280_Modulo
U$2: GPS; GPS_NEO-M8N
U$3: LORAE32; LoRa_E32
X1, X2: Borne_AK500-2

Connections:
3.3V: C1.1, C2.1, C3.1, C4.1, Capacitor100microF1.1, U1.J2_1, U$1.VCC, U$2.5V, U$3.5V, X2.2
ACIONA: D1.A, U1.J3_15
BUZZER: SG1.+, U1.J2_6
EXT_5V: U1.J2_19, X1.1
GND: C1.2, C2.2, C3.2, C4.2, Capacitor100microF1.2, LED1.K, LED2.K, R1.1, R1#2.2, SG1.-, U1.J2_14, U1.J3_1, U1.J3_7, U$1.GND, U$2.GND, U$3.GND, X1.2
L_VERDE: R3.2, U1.J2_7
L_VERMELHO: R4.2, U1.J2_8
unnamed: D1.C, Q1.1, R1.2
unnamed: Q1.2, R2.1
unnamed: LED1.A, R3.1
unnamed: LED2.A, R4.1
RX-GPS: U1.J3_11, U$2.RX
RX-LORA: U1.J3_4, U$3.RX
SCL: U1.J3_3, U$1.SCL
SDA: U1.J3_6, U$1.SDA
SKIB: R2.2, X2.1
Source: Q1.3, R1#2.1
TX-GPS: U1.J3_12, U$2.TX
TX-LORA: U1.J3_5, U$3.TX
